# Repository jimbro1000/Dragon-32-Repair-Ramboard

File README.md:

# Dragon32 Repair Ramboard
Plugin ram board for Dragon 32 Mk2 Issue 6, to replace 4116 chips with 4164 or 41256 chips

## State of Design
This is an _pre-release design_, yet to be fully tested. **Use at your own risk!**
The current version is v1.0.1 and has passed basic testing only

## Purpose
This project defines a hardware solution for replacing faulty 4116 16kx1bit
memory chips with the cheaper, more reliable 4164 64kx1bit design.

The aim is to minimise complexity of repair by providing a single plug-in
board with 16 socketed 4164 chips. To plug the 4164 chips in directly to
the Dragon board requires modifications to the chips due to slight
incompatibilities.

## Compatibility (read carefully)
The current design will **only** work with the Dragon 32 Mk2 Issue 6 
mainboard with 16 4116 chips. There are many variants of the mainboard so 
double check that the it is the right design.

To confirm it is correct there should a row of 9 chips across the top right
of the board (IC1-IC8 and IC43), a further row of 7 chips should be underneath 
it (IC36-IC42).

The board has two jumpers (JP1 and JP2) to allow configuration of how pin 1 of
the replacement memory chips is handled. By default the jumpers are bridged to
supply 5v to pin 1 for better compatibility with 4164 chips. Most will allow a
low or high signal but some demand that the pin is at 5v.

If you are using 41256 chips or suitable 4164 chips that jumper position can be
modified by cutting the bridge and soldering to the ground side of the jumper.
This facilitates the use of half-good chips (provided the same half is consistent
for each bank).

**Important:**
If you have an earlier D32 or a D64 (or one of the variants), this will _**not**_
fit. The design can be adapted to work but not in the current form.

## Ordering Boards ##
The design of the board is in Kicad 6 - I have not generated gerber files
for the pre-release. You will need to download this repository and open 
the files in a compatible package.

I've ordered early prototype boards from PCBWay and they work out at
approximately £22 for 10 boards (ordering less will not save any money
and just makes the individual boards more costly).

## Assembly
1. Fit two rows of long pin headers for IC1, IC36 and IC43 to the underside of the 
board, these are the left hand biased pads of each socket pair. Make the projection 
above the board as small as possible - some pin headers will allow the plastic 
spacer to slide (especially when warmed)
2. Fit pin headers for pin 2 and pin 14 for each of the remaining IC positions on 
the underside of the board. Make the projection above the board as small as possible
3. Trim the soldered pin headers down on the top side of the board to allow 
better clearance for the sockets
4. Check the JP1 and JP2 bridge positions are as desired, once the sockets are 
fitted it can be very tricky to modify the bridge
5. Fit 16 dip-16 sockets in the U1 to U16 positions on the top side of the board, 
these are the right hand of each socket pair (once fitted you should see a single 
column of pads between each socket). Trimming of the sockets may be necessary if 
the fitted pin headers are too high on the top side of the board. From experience 
applying pressure to the sockets will allow them to flatten against the board...
6. (optional) fit the 1k resistor and led (shows a live 5v connection to the 
board)
7. (optional) fit a 2-pin header on Vcheck for monitoring the voltage supplied to
the board

tip: If you fit the sockets to the main board first, these can be used to make 
sure the header pins align correctly before soldering them in. Care must be taken
to ensure alignment and position is correct and that stray solder splashes are not
left on the main board.

tip: If you have ordered multiple boards, use a blank board as a guide to keep the pins
tightly aligned to the correct pattern. 

## Fitting
1. remove (desolder) all 16 memory chips from the board
2. fit 16 dip-16 sockets in the positions left vacant by the memory chips
3. fit the repair board making sure that the pins line up correctly

note: only IC1, IC36 and IC43 have a significant number of pins and cannot
easily be misaligned. Only 2 pins should be fitted for the remaining
sockets for the Din and Dout pin positions

## BoM
| Item | Quantity | Positions |
|:-----|:--------:|:----------|
| dip-16 socket | 16 | U1-U16 |
| dip-16 socket | 16 | (recommended) IC1-IC8, IC36-IC43 (main Dragon board) |
| pin header 8x1 | | IC1, IC36, IC43 fully populated |
| pin header 1x1 | | IC2-IC8, IC37-IC42 pin 2, pin 14 |
| red led 5mm | 1 | (optional) D1 |
| 1k 0.25W resistor | 1 | (optional) R1 |
| pin header 2x1 | 1 | (optional) Vcheck1 |

## Contact
The project was created by Julian Brown.
Use the Facebook "Dragon 32/64 Owners/Users" group for contact

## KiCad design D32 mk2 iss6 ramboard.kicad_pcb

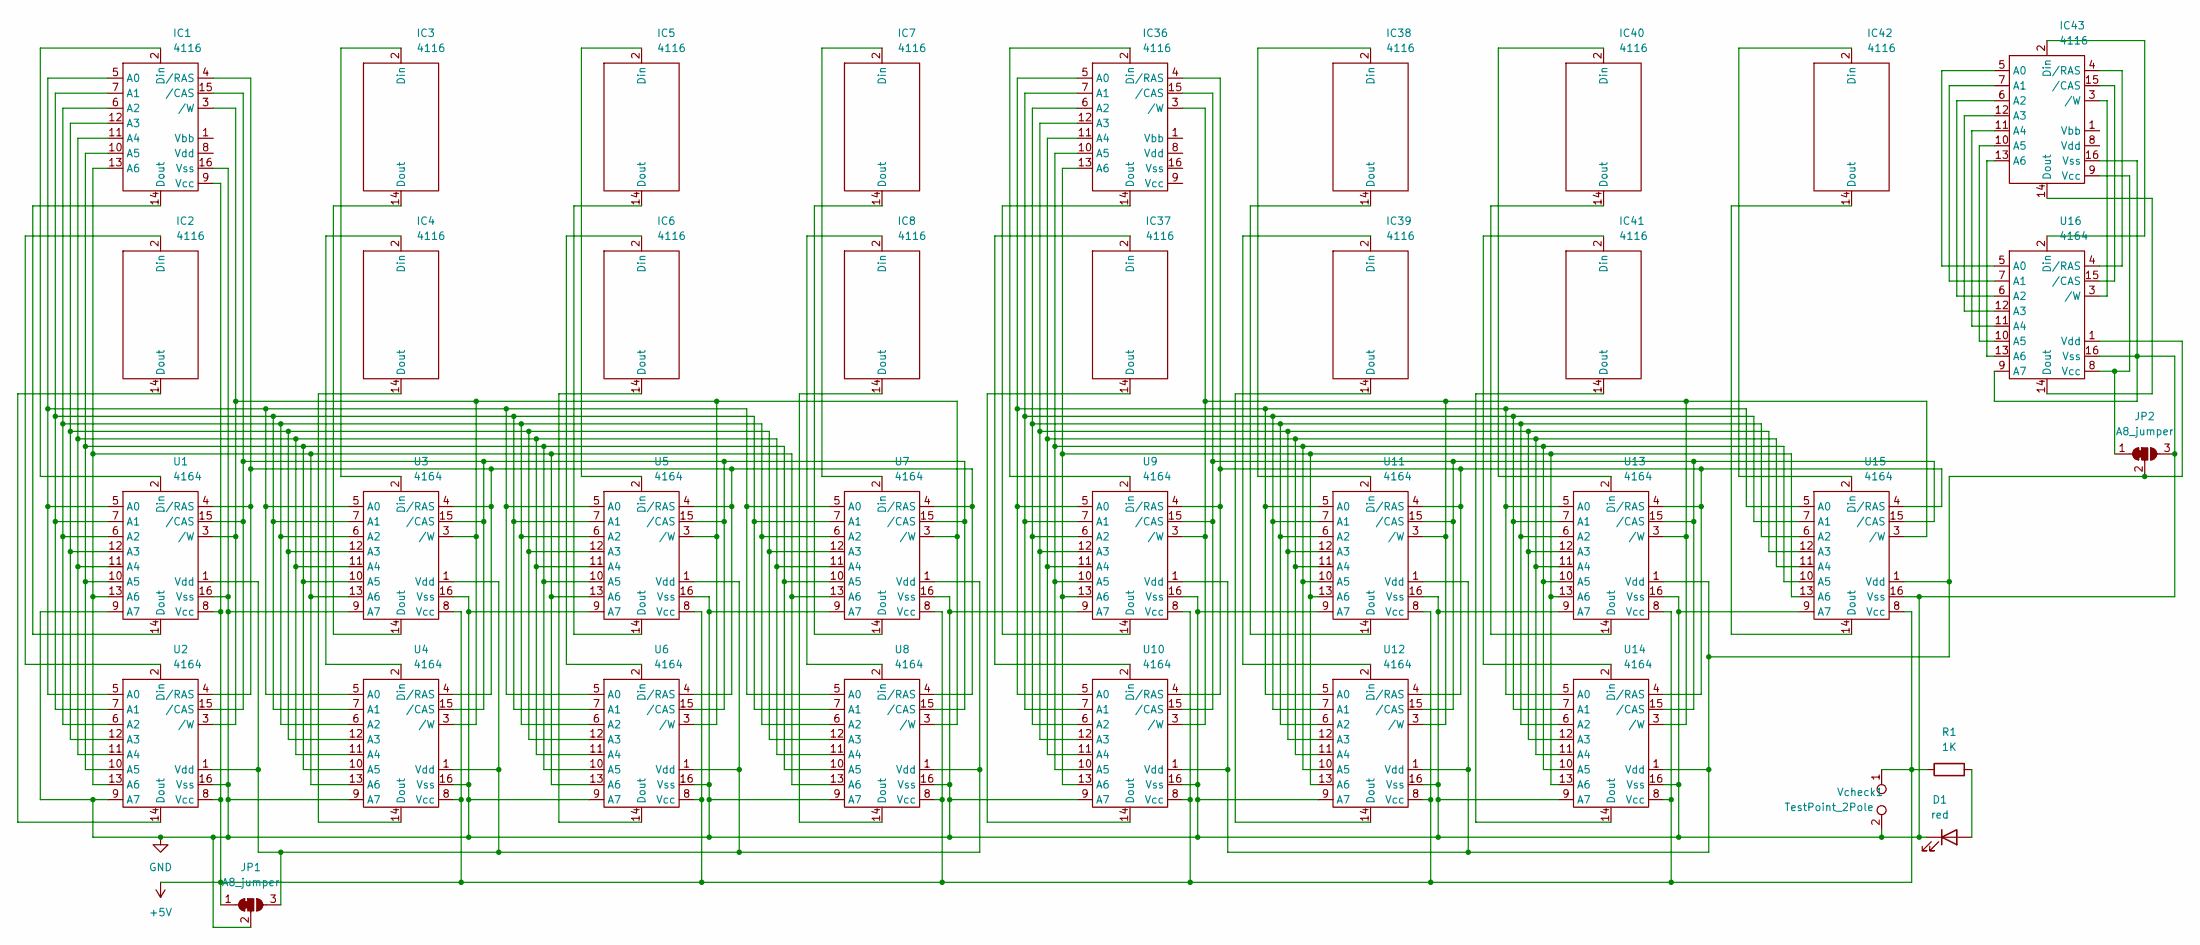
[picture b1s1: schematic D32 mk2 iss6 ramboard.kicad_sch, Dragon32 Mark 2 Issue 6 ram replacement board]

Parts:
D1: red; LED_D5.0mm
IC1, IC36, IC43: 4116; DIP-16_W7.62mm_Socket
IC2, IC3, IC4, IC5, IC6, IC7, IC8, IC37, IC38, IC39, IC40, IC41, IC42: 4116; 4116_Min_DIP-16_W7.62mm_Socket
JP1, JP2: A8_jumper; SolderJumper-3_P1.3mm_Bridged2Bar12_RoundedPad1.0x1.5mm
R1: 1K; R_Axial_DIN0309_L9.0mm_D3.2mm_P12.70mm_Horizontal
U1, U2, U3, U4, U5, U6, U7, U8, U9, U10, U11, U12, U13, U14, U15, U16: 4164; DIP-16_W7.62mm_Socket
Vcheck1: TestPoint_2Pole; TestPoint_2Pads_Pitch2.54mm_Drill0.8mm

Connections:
+5V: IC1.9 (Vcc), JP1.1 (A), R1.1, U1.8 (Vcc), U2.8 (Vcc), U3.8 (Vcc), U4.8 (Vcc), U5.8 (Vcc), U6.8 (Vcc), U7.8 (Vcc), U8.8 (Vcc), U9.8 (Vcc), U10.8 (Vcc), U11.8 (Vcc), U12.8 (Vcc), U13.8 (Vcc), U14.8 (Vcc), U15.8 (Vcc), Vcheck1.1
GND: D1.1 (K), IC1.16 (Vss), IC43.16 (Vss), JP1.2 (C), JP2.3 (B), U1.9 (A7), U1.16 (Vss), U2.9 (A7), U2.16 (Vss), U3.9 (A7), U3.16 (Vss), U4.9 (A7), U4.16 (Vss), U5.9 (A7), U5.16 (Vss), U6.9 (A7), U6.16 (Vss), U7.9 (A7), U7.16 (Vss), U8.9 (A7), U8.16 (Vss), U9.9 (A7), U9.16 (Vss), U10.9 (A7), U10.16 (Vss), U11.9 (A7), U11.16 (Vss), U12.9 (A7), U12.16 (Vss), U13.9 (A7), U13.16 (Vss), U14.9 (A7), U14.16 (Vss), U15.9 (A7), U15.16 (Vss), U16.9 (A7), U16.16 (Vss), Vcheck1.2
unnamed: D1.2 (A), R1.2
unnamed: IC1.2 (Din), U1.2 (Din)
unnamed: IC1.3 (/W), U1.3 (/W), U2.3 (/W), U3.3 (/W), U4.3 (/W), U5.3 (/W), U6.3 (/W), U7.3 (/W), U8.3 (/W)
unnamed: IC1.4 (/RAS), U1.4 (/RAS), U2.4 (/RAS), U3.4 (/RAS), U4.4 (/RAS), U5.4 (/RAS), U6.4 (/RAS), U7.4 (/RAS), U8.4 (/RAS)
unnamed: IC1.5 (A0), U1.5 (A0), U2.5 (A0), U3.5 (A0), U4.5 (A0), U5.5 (A0), U6.5 (A0), U7.5 (A0), U8.5 (A0)
unnamed: IC1.6 (A2), U1.6 (A2), U2.6 (A2), U3.6 (A2), U4.6 (A2), U5.6 (A2), U6.6 (A2), U7.6 (A2), U8.6 (A2)
unnamed: IC1.7 (A1), U1.7 (A1), U2.7 (A1), U3.7 (A1), U4.7 (A1), U5.7 (A1), U6.7 (A1), U7.7 (A1), U8.7 (A1)
unnamed: IC1.10 (A5), U1.10 (A5), U2.10 (A5), U3.10 (A5), U4.10 (A5), U5.10 (A5), U6.10 (A5), U7.10 (A5), U8.10 (A5)
unnamed: IC1.11 (A4), U1.11 (A4), U2.11 (A4), U3.11 (A4), U4.11 (A4), U5.11 (A4), U6.11 (A4), U7.11 (A4), U8.11 (A4)
unnamed: IC1.12 (A3), U1.12 (A3), U2.12 (A3), U3.12 (A3), U4.12 (A3), U5.12 (A3), U6.12 (A3), U7.12 (A3), U8.12 (A3)
unnamed: IC1.13 (A6), U1.13 (A6), U2.13 (A6), U3.13 (A6), U4.13 (A6), U5.13 (A6), U6.13 (A6), U7.13 (A6), U8.13 (A6)
unnamed: IC1.14 (Dout), U1.14 (Dout)
unnamed: IC1.15 (/CAS), U1.15 (/CAS), U2.15 (/CAS), U3.15 (/CAS), U4.15 (/CAS), U5.15 (/CAS), U6.15 (/CAS), U7.15 (/CAS), U8.15 (/CAS)
unnamed: IC2.2 (Din), U2.2 (Din)
unnamed: IC2.14 (Dout), U2.14 (Dout)
unnamed: IC3.2 (Din), U3.2 (Din)
unnamed: IC3.14 (Dout), U3.14 (Dout)
unnamed: IC4.2 (Din), U4.2 (Din)
unnamed: IC4.14 (Dout), U4.14 (Dout)
unnamed: IC5.2 (Din), U5.2 (Din)
unnamed: IC5.14 (Dout), U5.14 (Dout)
unnamed: IC6.2 (Din), U6.2 (Din)
unnamed: IC6.14 (Dout), U6.14 (Dout)
unnamed: IC7.2 (Din), U7.2 (Din)
unnamed: IC7.14 (Dout), U7.14 (Dout)
unnamed: IC8.2 (Din), U8.2 (Din)
unnamed: IC8.14 (Dout), U8.14 (Dout)
unnamed: IC36.2 (Din), U9.2 (Din)
unnamed: IC36.3 (/W), U9.3 (/W), U10.3 (/W), U11.3 (/W), U12.3 (/W), U13.3 (/W), U14.3 (/W), U15.3 (/W)
unnamed: IC36.4 (/RAS), U9.4 (/RAS), U10.4 (/RAS), U11.4 (/RAS), U12.4 (/RAS), U13.4 (/RAS), U14.4 (/RAS), U15.4 (/RAS)
unnamed: IC36.5 (A0), U9.5 (A0), U10.5 (A0), U11.5 (A0), U12.5 (A0), U13.5 (A0), U14.5 (A0), U15.5 (A0)
unnamed: IC36.6 (A2), U9.6 (A2), U10.6 (A2), U11.6 (A2), U12.6 (A2), U13.6 (A2), U14.6 (A2), U15.6 (A2)
unnamed: IC36.7 (A1), U9.7 (A1), U10.7 (A1), U11.7 (A1), U12.7 (A1), U13.7 (A1), U14.7 (A1), U15.7 (A1)
unnamed: IC36.10 (A5), U9.10 (A5), U10.10 (A5), U11.10 (A5), U12.10 (A5), U13.10 (A5), U14.10 (A5), U15.10 (A5)
unnamed: IC36.11 (A4), U9.11 (A4), U10.11 (A4), U11.11 (A4), U12.11 (A4), U13.11 (A4), U14.11 (A4), U15.11 (A4)
unnamed: IC36.12 (A3), U9.12 (A3), U10.12 (A3), U11.12 (A3), U12.12 (A3), U13.12 (A3), U14.12 (A3), U15.12 (A3)
unnamed: IC36.13 (A6), U9.13 (A6), U10.13 (A6), U11.13 (A6), U12.13 (A6), U13.13 (A6), U14.13 (A6), U15.13 (A6)
unnamed: IC36.14 (Dout), U9.14 (Dout)
unnamed: IC36.15 (/CAS), U9.15 (/CAS), U10.15 (/CAS), U11.15 (/CAS), U12.15 (/CAS), U13.15 (/CAS), U14.15 (/CAS), U15.15 (/CAS)
unnamed: IC37.2 (Din), U10.2 (Din)
unnamed: IC37.14 (Dout), U10.14 (Dout)
unnamed: IC38.2 (Din), U11.2 (Din)
unnamed: IC38.14 (Dout), U11.14 (Dout)
unnamed: IC39.2 (Din), U12.2 (Din)
unnamed: IC39.14 (Dout), U12.14 (Dout)
unnamed: IC40.2 (Din), U13.2 (Din)
unnamed: IC40.14 (Dout), U13.14 (Dout)
unnamed: IC41.2 (Din), U14.2 (Din)
unnamed: IC41.14 (Dout), U14.14 (Dout)
unnamed: IC42.2 (Din), U15.2 (Din)
unnamed: IC42.14 (Dout), U15.14 (Dout)
unnamed: IC43.2 (Din), U16.2 (Din)
unnamed: IC43.3 (/W), U16.3 (/W)
unnamed: IC43.4 (/RAS), U16.4 (/RAS)
unnamed: IC43.5 (A0), U16.5 (A0)
unnamed: IC43.6 (A2), U16.6 (A2)
unnamed: IC43.7 (A1), U16.7 (A1)
unnamed: IC43.9 (Vcc), JP2.1 (A), U16.8 (Vcc)
unnamed: IC43.10 (A5), U16.10 (A5)
unnamed: IC43.11 (A4), U16.11 (A4)
unnamed: IC43.12 (A3), U16.12 (A3)
unnamed: IC43.13 (A6), U16.13 (A6)
unnamed: IC43.14 (Dout), U16.14 (Dout)
unnamed: IC43.15 (/CAS), U16.15 (/CAS)
unnamed: JP1.3 (B), U1.1 (Vdd), U2.1 (Vdd), U3.1 (Vdd), U4.1 (Vdd), U5.1 (Vdd), U6.1 (Vdd), U7.1 (Vdd), U8.1 (Vdd)
unnamed: JP2.2 (C), U9.1 (Vdd), U10.1 (Vdd), U11.1 (Vdd), U12.1 (Vdd), U13.1 (Vdd), U14.1 (Vdd), U15.1 (Vdd), U16.1 (Vdd)

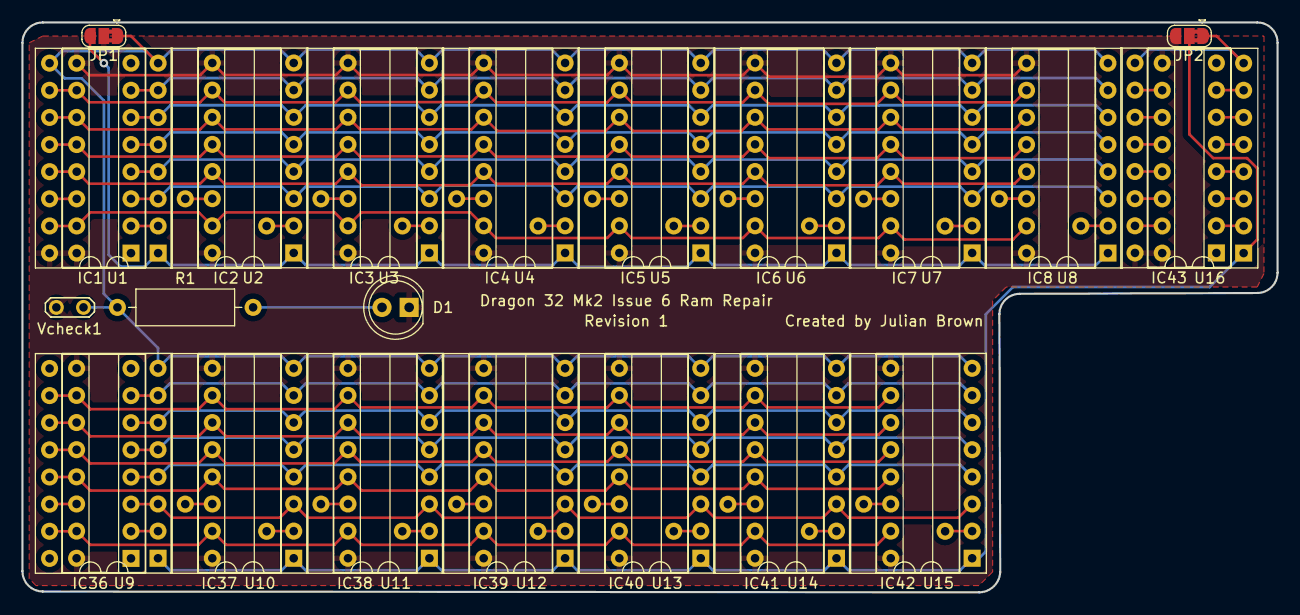
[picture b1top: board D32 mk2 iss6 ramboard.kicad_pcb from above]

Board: 2 copper layers, 117.5 x 53.3 mm, 37 parts (0 on the bottom side), 68 nets.

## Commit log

2022-02-09 feat: decouple power rail
2022-02-20 fix 4116 pin bindings
2022-02-20 correct 4116 pins and simplify networks
2022-02-20 move text to the right layer for silkscreen
2022-02-20 make A8 configurable on each bank
2022-02-20 update README for release
2022-06-14 update pcb
2022-06-14 add sram symbol 32kx8
